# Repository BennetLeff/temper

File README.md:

# Temper — ESP32-S3 Induction Cooker

## Architecture

> Package inventory — boxes sized by lines of code, colored by language, with dependency arrows. The Mermaid diagram below shows data-flow relationships.

Temper is a consumer induction cooker built around three pillars: an
**ESP32-S3 firmware** with an 8-state transition-table machine handling
real-time power control and hardware-latched protection circuits; a **KiCad
PCB design** optimized through a custom CP-SAT-based signal-integrity and
thermal-aware placer pipeline; and a **Python/Rust placer toolchain**
(CP-SAT solver, geometry/DRC/DSN/IPC crates, workflow DAG) that automates layout
and checks placement against IPC standards. Protection — over-current,
over-voltage, thermal shutdown, UVLO — is *designed* to be hardware-latched with
firmware monitoring.

> **Implementation status is deliberately not summarized here.** As of this
> writing not all protection gates are implemented, and none has been validated
> on hardware. [`docs/STRATEGY.md`](docs/STRATEGY.md) holds the measured state
> and the gate matrix; it churns by design, and this file does not restate it.
> An earlier version of this paragraph asserted that all safety gates were
> hardware-latched and monitored, which was not true when written.

```mermaid
graph TD
  subgraph Firmware ["Firmware (ESP32-S3, C)"]
    SM[8-State Machine]
    PROT[Protection Circuits<br/>OCP OVP THM UVLO]
  end

  subgraph PCB ["PCB (KiCad)"]
    KICAD[Schematics & Layout]
  end

  subgraph Placer ["Placer (Python + Rust)"]
    CPSAT[CP-SAT Solver]
    RUST[Rust Crates<br/>Geometry DRC DSN IPC PCL-IR]
  end

  subgraph Pipeline ["Pipeline & CI"]
    DAG[temper-workflow DAG]
    REGR[Placer Regression]
    FW[Firmware Tests]
    PY[Python Tests]
  end

  SM --> PROT
  CPSAT --> RUST
  KICAD --> DAG
  RUST --> DAG
  DAG --> REGR
  FW --> DAG
  PY --> DAG
```

## Get Started in 60 Seconds

Build and run the firmware test suite:

```bash
cmake -B firmware/test/build firmware/test
cmake --build firmware/test/build
./firmware/test/build/test_state_machine_only
```

Or build and test the placer toolchain:

```bash
uv sync
uv run pytest packages/temper-placer/tests/
```

**Prerequisites:** CMake ≥ 3.16 and the ESP-IDF toolchain (see
[CONTRIBUTING.md](CONTRIBUTING.md) for full setup instructions).

## Reading Paths

### 5-Minute Overview

For anyone wanting to understand what Temper is and how it's structured:

- [docs/STRATEGY.md](docs/STRATEGY.md) — project approach, safety and performance gates
- Architecture diagram above — subsystem relationships at a glance
- [Project structure](#project-structure) — what lives where

### 30-Minute Build & Test

For developers ready to build, test, and navigate the codebase:

- [CONTRIBUTING.md](CONTRIBUTING.md) — development workflow, commit convention, codegen rules
- [AGENTS.md](AGENTS.md) — firmware build section; codegen and CI conventions
- [`.importlinter`](.importlinter) — package boundary contracts; verify with `uv run python scripts/import_linter_gate.py`
- [packages/temper-placer/tests/regression/](packages/temper-placer/tests/regression/) — placer regression test suite

### Deep-Dive Contributor

For contributors working on architecture, verification, or toolchain internals:

- [AGENTS.md](AGENTS.md) — full agent instructions, traceability convention, physics verification rules
- [docs/plans/](docs/plans/) — feature and improvement plans with requirements trace
- [docs/solutions/](docs/solutions/) — documented fixes for past bugs, patterns, and tooling decisions
- [docs/TRACEABILITY.md](docs/TRACEABILITY.md) — requirements-to-code traceability specification
- [docs/physics-verification-methodology.md](docs/physics-verification-methodology.md) — CP-SAT constraint soundness and validation framework

## Project Structure

<!-- BEGIN GENERATED: repo-map -- edits here are overwritten by scripts/gen_repo_state.py -->

*All 22 tracked top-level directories. Generated -- a new directory without a description fails CI.*

| Directory | Purpose |
|---|---|
| `.cargo/` | Cargo config -- macOS pyo3 `-undefined dynamic_lookup` link flags |
| `.github/` | CI workflows, issue templates, code owners |
| `benchmarks/` | CP-SAT benchmark harness and external board corpora manifests |
| `ci-corpus/` | Gate-mutation-testing corpus (canaries + mutations.yaml) for CI gates |
| `components/` | Local KiCad symbol/footprint libraries, one directory per part |
| `configs/` | Named placer configurations (deterministic, production) |
| `crates/` | Rust-only crates -- no pyproject.toml, outside the uv workspace. Where code lives once it no longer needs an interpreter: the temper binary and the CP-SAT FFI |
| `dashboard/` | Static HTML/JS dashboard for placer metrics |
| `datasheets/` | Vendor PDFs for parts used in the design |
| `docs/` | Plans, brainstorms, solutions, evidence, specs, and strategy |
| `elec/` | Atopile electrical source -- the schematic's source of truth |
| `firmware/` | ESP32-S3 firmware (C), 8-state machine and protection monitoring |
| `instruments/` | Measurement instrument designs, calibration procedures, and prototype fabrication files |
| `max31865/` | KiCad library for the MAX31865 RTD front-end (predates components/) |
| `metrics/` | Recorded routing/placement metric snapshots (JSON) |
| `output_gerbers/` | Exported Gerber/drill artifacts from a past routed revision |
| `packages/` | Python and Rust workspace members -- placer, DRC, geometry, router |
| `pcb/` | KiCad project: schematics, board, and project settings |
| `power_pcb_dataset/` | Regression corpus, baselines, and DRC ceilings |
| `scripts/` | CI gates, generators, and one-off analysis tooling |
| `simulation/` | ngspice models and protection-gate simulation harnesses |
| `tools/` | Developer utilities not wired into CI gates |

<!-- END GENERATED: repo-map -->

## Inventory

<!-- BEGIN GENERATED: inventory -- edits here are overwritten by scripts/gen_repo_state.py -->

**18 workspace packages** under `packages/`:

- `temper-constraint-compiler`
- `temper-data-model`
- `temper-design-bundle`
- `temper-drc-rs`
- `temper-geometry`
- `temper-io-types`
- `temper-orchestration`
- `temper-pcl-ir`
- `temper-placer`
- `temper-py-bridge`
- `temper-py-bridge-derive`
- `temper-quality-oracle`
- `temper-rust-router`
- `temper-rust-router-core`
- `temper-thermal`
- `temper-wasm-test-runner`
- `temper-worker`
- `temper-workflow`

Sizes and dependency edges are in [`ARCHITECTURE.svg`](./ARCHITECTURE.svg), regenerated automatically on push.

<!-- END GENERATED: inventory -->

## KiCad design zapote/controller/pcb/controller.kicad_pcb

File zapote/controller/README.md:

# Integrated SELV controller (schematic capture)

This is the induction cooktop's low-voltage controller, captured in atopile and laid out (layout L3: enclosure R33 delta on the R31 outline, the R36 rim NTC, and the L3 blower supply, NTC filters and thermal trip ladder; see [LAYOUT.md](LAYOUT.md)). The board integrates:
- an ESP32-S3-WROOM-1U-N8 (U.FL to an off-board chip antenna, enclosure R33);
- the interlock and thermal-sense circuits, ported unchanged;
- the RTD front end;
- the D-11 bus-voltage receiver;
- the buffers for the ADC channels;
- the 3.3 V supply and the adjustable 5.5–12 V blower supply with tach (L3, DECISIONS C28), the blower buck fed from its own 15 V supply PS3 through J13 (stage 16, C33);
- the probe connectors and one 12-way UI bus (J7, R33) to the fascia UI board, which carries the OLED, buttons, encoder and buzzer.

It draws all of its power from PS3 on J13 (C49: the logic rail `v15_selv` is fed from `V15_BLW` through D9, SS14) and supplies native-21's 3.3 V logic back through J4.3. J4.1 is not a supply since C49: it is `bias_good_j4` from the power board, read on GPIO35.

**Status:** schematic source, frozen netlist and a routed, DRC-clean layout candidate (0 errors, 0 unconnected, schematic parity 0; DFM, enclosure checks and fab review PASS) with a JLC fab package ([LAYOUT.md](LAYOUT.md)). **Candidate, not released**: ordering is the owner's decision. Not fabricated, no physical test. Open items and decisions are in [DECISIONS.md](DECISIONS.md). The connector list and placement note for the enclosure team are in [ENCLOSURE-HANDOFF.md](ENCLOSURE-HANDOFF.md).

**Requirement inputs** (read-only):
- `output/temper-manufacturing-r25/design/r25/CONTROLLER-ARCHITECTURE.md` and `CONTROLLER-SPEC.md`. They supersede r24 only in the harness landings.
- The R20 M1/M3, R21 N8 and R24 decisions.
- The native-21 J4 contract on branch `codex/power-stage-integration` @ `7c55c9ab8`, frozen into [inputs/native-21/](inputs/native-21/) with hashes in `provenance.json`. This covers `FAULT-INTERFACE.md`, DECISIONS (bus sense D-11, timing D-20, LINE_ZC, the 15 A input cap with its correction) and `firmware/components/power/include/{fullbridge_adapter,input_limits,line_zc}.h`.

## Layout of the unit

| Path | What |
|---|---|
| `elec/src/controller.ato` | Top module `SelvController`. One section per sheet: J4, power, trip glue, interlock, thermal, RTD, analog, MCU |
| `elec/src/controller_parts.ato` | New parts. Each docstring cites the datasheet pin table it was checked against |
| `elec/src/interlock_block.ato`, `thermal_block.ato` | Ported blocks, generated by `tools/port_blocks.py` (see below) |
| `elec/src/rtd_c1_block.ato` | `RTDSensingC1` (C37): the library `RTDSensing` plus the sensor-r3 CR-1 edits, generated by `tools/port_rtd_c1.py` (`--check` in the verifier) |
| `evidence/sensor-r3-checks/` | sensor-r3 `checks.py` (copied from sensor-c1-impulse-mining 1431caad5) and `run_as_built.py`, which runs it on the frozen netlist's values (`checks-as-built.json`) |
| `elec/src/{components,modules,footprints,interfaces,constraints,fac_utils}.ato`, `generics/` | Shared library, byte-identical to the RTD unit's source-04 set (`RTDSensing` lives in `modules.ato`) |
| `frozen/` | Reviewed build outputs (`default.net`, `default.csv`, `resolved-components.json`) with the unit path normalised to `UNIT`, plus `build-receipt.json` |
| `bom/controller-parts.json` | Every MPN with its LCSC code, JLC stock on 2026-10-08, origin and datasheet basis |
| `inputs/native-21/` | Frozen native-21 netlist, BOM and resolved export (the J4 and v3v3 counterpart) |
| `tools/verify_controller.py` | The verification (below); writes `evidence/verify.json` |
| `tools/controller_calcs.py` | Every numeric claim in these docs; writes `evidence/controller_calcs.json` |
| `tests/test_verify_mutations.py` | 50 tests. They miswire the frozen netlist and require the owning check to fail |
| `layout/` | Board build, router, enclosure/layout check, DFM gate and fab export; `python3 layout/make.py` runs the gates (see [LAYOUT.md](LAYOUT.md)) |
| `pcb/` | `controller.kicad_pcb` (routed board), `.kicad_pro`, the parity schematic, vendored footprints |
| `fab/` | Gerbers, drill, BOM/CPL with LCSC codes, assembly drawing, `fab-notes.md` (candidate, not released) |

**What "ported unchanged" means here:** `tools/port_blocks.py` copies `zapote/interlock/source-build-02/.../interlock_unit.ato` and `zapote/thermal-sense/source-build-02/.../thermal_sense_unit.ato` with one line filter. It drops only:
- the standalone inter-board headers (interlock J1/J2, thermal-sense J3);
- their pin joins;
- thermal-sense's `+3V3`/`gnd` net-name overrides.

`--check` proves that the committed files equal *source minus those lines*. The thermal probe connectors stay. Every value, MPN and internal connection is unchanged. `RTDSensing` is instantiated directly from the byte-identical library, so the RTD unit's 2×5 host header is not used.

## Build, freeze, verify

From `zapote/controller`. These use pinned atopile, are offline and build no Rust or workspace.

```sh
python3 tools/freeze.py            # ato build + circuit_export + normalise into frozen/ + receipt
python3 tools/freeze.py --check    # rebuild; fail if frozen/ is stale ("frozen fresh")
python3 tools/verify_controller.py # all checks on frozen/; exit 1 on any failure
python3 -m unittest discover -s tests -v
python3 tools/controller_calcs.py  # numeric basis only
python3 tools/snapshot_native21.py # re-derive inputs/native-21 from git (read-only)
```

- **Raw build:** `uv tool run --offline --from atopile==0.2.69 ato --non-interactive build elec/src/controller.ato:SelvController`.
- **Warnings:** the build emits only atopile's "Implicit Declaration" deprecation warnings for `override_net_name`, the same as the thermal-sense build.
- **Part identity:** it comes from `resolved-components.json` or the CSV, never from the netlist's `libsource` field. Atopile 0.2.69 aliases parts by footprint there; see the power-stage README.

**Current result** (frozen netlist sha256 `8471186c…`; 343 components, C51/C52): `VERIFY: PASS` (270 checks in 17 sections), and 50/50 mutation tests pass (2026-11-27).

| Section | Checks | What is asserted |
|---|---|---|
| sources | 5/5 | Ports equal their sources minus the boundary lines; `rtd_c1_block.ato` equals the library `RTDSensing` plus the listed C37 edits (`port_rtd_c1.py --check`). Library `modules/components/footprints.ato` hashes equal `zapote/rtd/circuit/rtd_contract.json` |
| j4 | 35/35 | All 16 pins carry exactly native-21's J4 net names. Both ends are Micro-Fit 3.0 2×8 headers (controller: right-angle 43045-1600 per R27; native-21: vertical 43045-1612) on a 1:1 harness. Pin obligations: J4.3 is the 3.3 V buck output; J4.1 feeds the 3.3 V buck only (stage 16: the blower buck is on PS3); each PWM line has a 10 kΩ pull-down and is driven from an MCU GPIO; PERMIT's only driver is the PERMIT gate U37 = latch Q AND RUN_EN (C23); bus_fault enters the interlock OCP input with its 10 kΩ pull-up; 11/12 enter the D-11 receiver; ct_mon sees one buffer input and ≥ 1 MΩ DC; ct_zc/line_zc reach GPIO38/39; returns 2/4/15 are on selv_gnd |
| adc1 | 26/26 | VBUS, CT_MON, HS, COIL, M12 and RIM (R36 rim NTC, GPIO9) each on one ADC1 pad, driven by its buffer; each NTC buffer input is an RC ≤ 1 kHz (C29). Six distinct channels; nothing analog on ADC2 or a strap; SPI 10–13 go to the RTD front end; the sample pattern fits (below) |
| trip | 24/24 | The structural and exhaustive interlock checks (below), with the C38 wiring: window branch on J3.2, runaway divider on J3.3, RTDIN± reaching J3 through the two-stage filter, the rim trip comparator's inputs |
| sensor_io | 6/6 | C37/C40: every J3 pin has its 220 nF and TVS to selv_gnd; J12 = RIM_SENSE / return / drain; each TVS's VRWM covers its line's maximum |
| capmode | 27/27 | C39 capacitive-mode detector: clocks from the inverted leg-A commands, D = CT_ZC through the polarity XOR, RUN_EN preset/clear, CAP_FAULT into the interlock OVP input, read-backs; a netlist-driven sequence simulation (inductive never faults, capacitive faults on the first edge, stuck / reversed CT, RUN_EN clears); the `capmode()` timing checks |
| v3v3 | 5/5 | Current budget for both boards, regulator, inductor, PS1 (logic only since stage 16: 4.83 W of 21 W at any blower speed), and the native-21 rail window |
| blower | 13/13 | J10 = V_BLOWER / GND / FG; FG pull-up, TVS and series R into GPIO3; GPIO46 PWM filtered into the blower buck's FB with full speed at reset; switch-off from expander P15 with the blower running at power-up; the `blower_supply()` sizing checks (C28) |
| blwin | 16/16 | Stage 16 (C33): J13 = V15_BLW / selv_gnd on a B2P-VH; U2's VIN, EN-divider top and input caps on V15_BLW; no part joins V15_BLW to v15_selv; 100 µF bulk on V15_BLW; BLW_PG 20 k / 4.7 k into expander P16; the `ps3_budget()` and `blw_pg()` checks (PS3 39.7 W of 60 W) |
| thermal | 11/11 | The thermal-sense comparator trips from the netlist resistor values, 64 corners (a port of the zapote-erc method): heatsink 101.4 °C (98.3–104.6) above the 95 °C firmware trip and with Tj ≤ 135 °C; coil 175.7 °C (169.7–182.0) above the 165 °C firmware trip; open/short margins (C32) |
| hs_adc | 9/9 | CR-8 (C45): HS_ADC = follower × r_hs_adc_bot / (r_hs_adc + r_hs_adc_bot) from the netlist values. The gain band (0.1 % + 25 ppm/K over 65 K) keeps the ADC below the calibrated 2.9 V from −40 to 150 °C at the 3.367 V rail (worst 2.877 V). Also checked: source and sampling error ≤ 0.1 K at 95 °C, follower load ≤ 1 mA. HS_SENSE carries exactly the thermal block's parts and r_hs_filt, so the hot and open comparators are untouched |
| ct_rms | 20/20 | The tank-RMS channel: ct_mon buffer → AC coupling → AD8436 (unity input buffer, AC-coupled core, single supply on v15, C0G CAVG) → gain-4 output buffer → 1 kΩ + BAT54S clamp → MCP3202 CH0. CH1 reads the LM4040 2.5 V reference. The ADC sits on the RTD SPI bus with its own pulled-up CS GPIO; the raw ct_mon ADC1 path is kept |
| ui | 25/25 | J7 (R33 UI bus, DECISIONS C26): exact 12-pin map with a GND beside every signal; each signal reaches its GPIO through one 33–100 Ω series resistor with nothing active on the connector side, and has an SRV05-4 clamp; the UI bus GPIOs (40/41/44/47/48/45) are disjoint from the RTD / MCP3202 SPI bus, which never reaches a connector; both chip selects pulled up; +5 V from the TLV76050 within its budget |
| bom | 2/2 | Every resolved MPN is in `bom/controller-parts.json` with a basis |
| misc | 8/8 | GPIO0 is pulled up and GPIO45/46 read 0 at reset; the PWM GPIOs have no reset pull-up; USB is on the TC2050 debug land; no switch on the board; EN and IO0 reach no connector but that land (C41) |

## Interlock trip path (hardware only)

**How the check works.** `verify_controller.py` builds a gate-level model from the captured netlist: LVC14, HC30, LVC1G74, the LVC1G08/32/38/14 gates and the LVC244 buffer, keyed by MPN pin tables. Comparators, supervisors, J4.10, the MCU and the I²C expander become free variables. The pass criterion is an **independent specification** of each source's healthy level (`tools/trip_sim.py`, `HEALTHY_LEVEL`), never the circuit's own internal nets.

**Structural checks:**
- PERMIT (J4.9) has one driver, the AND gate U37 (SN74LVC1G08): **PERMIT = latch Q AND RUN_EN** (DECISIONS C23). It has a 10 kΩ pull-down here (R103), and native-21 adds two 100 kΩ. The latch Q (`PERMIT_LATCH`) keeps the block's own 10 kΩ pull-down.
- The only firmware-driven nets in PERMIT's fan-in cone are `IL_RESET_N` (GPIO17, the reset request) and `RUN_EN` (GPIO14). RUN_EN feeds only the PERMIT gate (checked), has a 4.7 kΩ pull-down and no pull-up, and sits on a GPIO with no reset pull-up, so it reads "not permitted" at reset and with the MCU unpowered.
- No MCU or expander pin touches any other cone net. The MCU reads PERMIT, bus_fault, the supervisor output, RAIL_OK, LATCHED_FAULT and the three block faults only through the SN74LVC244A, so no GPIO misconfiguration can drive a protective net.
- The runaway comparator observes J3.2 (the connector-side S+) through the RTD block's window branch, and its threshold comes from the BIAS divider returned to J3.3 (S−, C38); the rim trip comparator compares the filtered rim NTC node with a v3v3 divider (checked, because comparators are free variables).
- The rail supervisor senses v3v3, and the watchdog's WDI is the MCU heartbeat.

**Exhaustive check.** All 2¹⁴ source combinations (C38 adds the rim trip, C39 the two capacitive-mode flip-flop outputs) × latch state × every RESET_N transition × RUN_EN (262 144 cases) were enumerated:
- every case with any source unhealthy leaves **PERMIT low**, whatever firmware does;
- PERMIT is never high while the latch is tripped or RUN_EN is low (`run_en_alone_cannot_assert_permit`): RUN_EN can only remove permission;
- all-healthy plus a fresh RESET_N falling edge with RUN_EN high grants PERMIT;
- all-healthy with no edge holds the latch state.

**Single-cause truth table.** Each row has every other source healthy and RUN_EN high, and starts from PERMIT high. The result is identical for RESET_N held low, held high, falling or rising.

| Trip source (net → interlock input) | Fault level | PERMIT | LATCHED_FAULT |
|---|---|---|---|
| J4.10 `bus_fault` (native-21 OR of OCP, OVP, HOT5, CT±; an open wire reads high via the 10 kΩ pull-up) → OCP | high/open | 0 | 1 |
| `CAP_FAULT` (C39): a capacitive-mode sample on a leg-A turn-off (U42 1Q̄ or 2Q) → OVP input | high | 0 | 1 |
| thermal `HS_HOT` or `HS_OPEN` → HS_FAULT (LVC1G32) → heatsink | high | 0 | 1 |
| thermal `COIL_HOT` or `COIL_OPEN` → COIL_FAULT → coil | high | 0 | 1 |
| RTD low/high window out of range, or `RTD_RAIL_OK` low → RTD_HW_FAULT (open-drain NAND) → RTD | low | 0 | 1 |
| `RUNAWAY_FAULT`: pan ≥ 298.8–323.1 °C (C38), MAX31865 BIAS off, or RTD open; or the rim NTC ≥ 262.1–288.3 °C or shorted (U40, C38) → runaway | high | 0 | 1 |
| `RAIL_OK` low (v3v3 outside 3.146–3.190 / 3.408–3.456 V, or within 10 ms of start-up) → RAIL_FAULT → AUX, and SENSOR_LIVE low | low | 0 | 1 |
| `RTD_RAIL_OK` low (RTD_AVDD below its 3.05 V supervisor) → SENSOR_LIVE low (and RTD_HW_FAULT) | low | 0 | 1 |
| Supervisor run-OK `WDT_RESET_N` low (TPS3823: WDI not toggled within 0.9 s minimum, or VDD below its 2.83–3.00 V threshold, SLVS165O) | low | 0 | 1 |
| All healthy, RESET_N held | — | holds | holds |
| All healthy for ≥ 1 ms, then a fresh RESET_N falling edge | — | 1 | 0 |

The simulation treats the sources as independent. Physical paths that make several assert together, like v3v3 loss, are covered by the FMEA in DECISIONS.md.
- **Loss of v3v3 or selv_gnd, or J4 unplugged:** the latch loses supply, the controller's 10 kΩ and native-21's 100 kΩ pull-downs take PERMIT low, and a broken J4.10 conductor reads as a fault.
- **Firmware reach:** it can read the latch, request a reset edge and drop RUN_EN (a fast stop that removes PERMIT without tripping the latch). It cannot hold the latch clear, assert PERMIT while the latch is tripped, or override a trip.

## Power tree

```
PS3 15 V on J13 V15_BLW ── D9 SS14 (C49) ── v15_selv ── 100 µF + 2×(10 µF‖100 nF)    [logic only, 4.83 W]
  ├─ U1 TPS62933F (FCCM, 500 kHz, EN UVLO on 10.9–12.1 V, off ≥ 9.8 V), 10 µH, 3×22 µF
  │    └─ v3v3 3.304 V nom (3.242–3.367 V, 0–85 °C)
  │         ├─ ESP32-S3-WROOM-1U-N8, J7.2 to the UI board (OLED, expander, encoder, buzzer), expander, buffers, D-11 receiver, MCP3202
  │         ├─ interlock / thermal-sense / RTD blocks (RTD analogue behind its ferrite → RTD_AVDD)
  │         ├─ U3 TPS3703A4330-Q1 window supervisor (SENSE via 1 k / 1 µF) → RAIL_OK
  │         └─ J4.3 → native-21 SELV logic (u_fault_or, 4× ISO7710, AMC1311 VDD2, UCC21550 VCCI …)
  ├─ U14 AD8436 tank-RMS converter (single supply, ≈ 0.64 mA)
  └─ 2 × 100 Ω → U16 TLV76050 → V5_UI (J7 pin 1, ≤ 30 mA for a 5 V encoder; current-limited)

PS3 MPM-90-15ST (chassis, 15 V, 85 W; C51; IRM-60-15ST at stage 16, C33) ── J13 (B2P-VH) V15_BLW ── 100 µF + 3 input caps
  ├─ 20 k / 4.7 k → BLW_PG → expander P16 (PS3 present)
  └─ U2 TPS62933 (500 kHz), 10 µH SWRB1205S, 2×22 µF → V_BLOWER 5.0–12.4 V (PWM into FB) → J10 blower (1.42 A typ, 2.70 A max)
       EN defaults on (UVLO follows PS3); firmware sets speed (GPIO46 PWM, full speed by default) and can switch it off (Q1 from expander P15)
```

**v3v3 budget**, from datasheet maxima at 3.465 V (`evidence/verify.json`, rows per part):

| Load | mA |
|---|---|
| Controller board, all parts on v3v3. Includes the ESP32 at 500 mA (Espressif's ≥ 0.5 A supply requirement; TX peak 355 mA), MAX31865 9.65 mA with BIAS, OPA2388 5.2 mA, the interlock WDI 1 kΩ pull-down 3.5 mA, and pull-ups at full current | 537.3 |
| native-21 on J4.3 and on controller-driven J4 lines (UCC21550 VCCI, AMC1311, 4× ISO7710, DIS pull-ups, INx 50 kΩ min, PERMIT gate networks). Computed from its frozen netlist; every v3v3 part must be modelled or the check fails | 49.4 |
| OLED NHD-3.12-25664UCW2 on the UI board via J7.2, 100 % on (Newhaven IDD max) | 340 |
| UI board allocation on J7.2 [UNVERIFIED parts]: 30 mA logic + 3.3 V encoder option, 90 mA buzzer (the 5 V option is also counted on 15 V in the PS1 figure) | 120 |
| **Peak** | **1047** |

- **Converter limits:** the TPS62933F is good for 3 A and SWPA6045S100MT for 2.45 A Irms (3.5 A sat).
- **PS3 (C49, logic and blower on one supply):** merged continuous load 44.55 W against 65 W, 99 % of the 45 W 60 °C derated figure (`tools/controller_calcs.py` `merge_rail`; DECISIONS C49). The PS1 figures that stood here were for the pre-C49 board, which had a separate 21 W logic supply.
- **Own load:** with the fan excluded, the controller's own load stays under the spec's ≈ 4 W even at peak.
- **Native-21's rail:** it sees 3.237–3.389 V at its J4.3. That covers regulator tolerance, the J4 harness (≤ 1 m AWG22, two 10 mΩ contacts per conductor; an allocation, because the harness isn't specified) and ground shift from the 15 V return. This is inside the 3.135–3.465 V contract.

**Rail window** (`tools/controller_calcs.py`):
- **Thresholds:** the TPS3703A4330 trips UV at 3.146–3.190 V and OV at 3.408–3.456 V, both inside the contract.
- **Regulator corners:** the low corner clears the UV *release* threshold (≤ 3.217 V) by 21 mV, so RESET always releases after start-up.
- **Margins left** for excursions slower than the 1 ms SENSE filter: 47 mV (low) and 39 mV (high). Faster Wi-Fi/OLED load steps are filtered.
- **Bench item:** measure supervisor nuisance trips under combined ESP32-TX and OLED-on steps.

## ADC1 and sampling

| GPIO | ADC1 | Signal | Source | Attenuation |
|---|---|---|---|---|
| 1 | CH0 | CT_MON_ADC | TLV9062 follower of J4.14 ct_mon (≥ 10 MΩ DC load), 100 Ω / 1 nF | ATTEN3 (0–2.9 V) |
| 2 | CH1 | VBUS_ADC | D-11 OPA2388 half-gain difference receiver, 100 Ω / 100 nF | ATTEN2 (0–1.6 V) |
| 6 | CH5 | HS_ADC | TLV9062 follower of thermal-sense HS_SENSE | ATTEN3 |
| 7 | CH6 | COIL_ADC | TLV9062 follower of COIL_SENSE | ATTEN3 |
| 8 | CH7 | M12_ADC | TLV9062 follower of the M12 probe divider | ATTEN3 |

**Free ADC1 pads:** GPIO3, 4, 5, 9 and 10 are used digitally. GPIO3 is fan tach (a strap, harmless unless the JTAG eFuse is burnt). GPIO4/5 are PWM, GPIO9 is I²C SDA and GPIO10 is RTD CS. So **ADC1 is full**: the tank-RMS signal therefore goes to an external MCP3202 on the RTD SPI bus (below).

**Tank RMS (external ADC).** U14 AD8436BRQZ converts the buffered ct_mon to true RMS. Its datasheet gives 65 kHz for 1 % additional error at 300 mV rms, against a 31–55 kHz tank band.
- **Scaling:** a gain-4 output buffer puts 22 A RMS tank at 1.32 V (1606 codes) and the 55 A peak trip at 2.33 V.
- **Errors:** coupling error at 31 kHz is 0.002 %; Schottky leakage contributes ≤ 0.15 %.
- **Settling:** CAVG = 100 nF C0G gives an estimated 3.4 ms to 0.1 %, falling. That is the datasheet's 10 µF figure scaled linearly; the scaling is an assumption to bench-check. It is within the 8.3 ms half-cycle.
- **ADC:** U15 MCP3202 CH0 reads it; CH1 reads the LM4040A25 2.5 V (0.1 %) so firmware removes the v3v3-as-reference error. CS is GPIO42. The bus stays on the board; the UI board has its own SPI host (C26).
- **Why not ADC2:** the free ADC2 pads are the debug USB pins, and ADC2 cannot be read while Wi-Fi runs.

The raw ct_mon ADC1 path stays for phase and waveform checks.

**Sampling plan.** It is checked against ESP-IDF v5.2.3 `SOC_ADC_SAMPLE_FREQ_THRES_HIGH` = 83 333 S/s and the datasheet's 100 kS/s.
- **Continuous pattern** at 80 kS/s: `VBUS, CT_MON, VBUS, CT_MON, VBUS, HS, COIL, M12, RIM` (RIM: R36 rim NTC, C27).
- **Resulting rates:** VBUS 26.7 kS/s (≥ 20 kS/s required) with a largest gap of 62.5 µs (≤ 150 µs freshness), CT_MON 17.8 kS/s, and the four temperatures 8.9 kS/s each.

**D-11 receiver:**
- **At the ADC:** 0.248 V at 0 V bus, 0.956 V at 170 V and 1.073 V at 198 V.
- **Over-range:** the 1210 mV over-range latch corresponds to a 231 V bus.

## Part choices (summary; the reasons are in DECISIONS.md)

| Function | Part | Why |
|---|---|---|
| MCU | ESP32-S3-WROOM-1U-N8 (C2980297) | Required family (the round-5 firmware targets the S3-WROOM-1-N8; the -1U has the same pins). No octal PSRAM, so GPIO35–37 are free. R33: U.FL to the off-board chip antenna |
| 3.3 V | TPS62933FDRLR (C5219272) | 3.8–30 V, 3 A, ±1.5 % VFB. Forced-CCM gives predictable ripple. Shares a die with the fan buck |
| Blower supply | TPS62933DRLR (C3200405) + SWRB1205S-100MT 10 µH (C169383) | 3 A class, 4.2–5.8 A high-side limit; the 4 A-rated inductor carries the blower's 2.70 A maximum. Speed by PWM into FB; full speed by default (C28) |
| Rail window | TPS3703A4330DSERQ1 (C1850327) | ±0.7 % fixed ±4 % window, the only class that fits inside 3.135–3.465 V around a ±1.5 % regulator. The TPS3700 (±1.7 %) does not. Q1 grade fitted because the commercial part had zero JLC stock; SBVS344D confirms identical pins, thresholds and delay |
| Tank RMS | AD8436BRQZ (C652840) | Datasheet bandwidth 65 kHz for 1 % error, the only candidate whose datasheet I could read that covers 55 kHz on our supplies. The LTC1968 is 500 kHz per ADI's product page, but its 4.5–5.5 V supply and unread datasheet ruled it out. **JLC stock 0: consign** |
| External ADC | MCP3202-CI/SN (C56997) | 2-channel 12-bit SPI at 3.3 V; shares the RTD bus |
| UI bus protection | 6 × 100 Ω series, 2 × SRV05-4 (C2836319), TLV76050 (C2867465) | Source termination and ESD current limit on a 120 mm jumper; ±12 kV contact clamps; ≤ 30 mA +5 V for a 5 V encoder |
| Bus receiver | OPA2388IDR + LM4040A25 + RT0603 0.1 % | The D-11 circuit as specified |
| Analog buffers | 2× TLV9062IDR (C398355) | CMOS, 0.5 pA typical bias. Gives the thermal-sense nodes a receiver that stays within their ±1 µA budget and isolates ADC switched-capacitor kick |
| Read-back isolation | SN74LVC244APWR (C7668) | One part buffers all eight protective read-backs; Ioff |
| SENSOR_LIVE, AUX | SN74LVC1G08, SN74LVC1G14 | — |
| Runaway | TLV3201AIDBVR + RT0603 20k/10k 0.1 % | Same comparator as the RTD and thermal blocks |
| I/O expander | TCA9555PWR (C465732) | Four fault read-backs and RTD_DRDY; P00–P06, P14–P17 spare since R33 |
| J4 | Molex 43045-1600 right-angle (C277731) | R27: right edge, mating +X; same Micro-Fit circuit numbering as native-21's 43045-1612. Envelope fit against Molex's drawing is [UNVERIFIED] (drawing not reachable) |
| UI bus (R33) | JST B12B-XH-A (C158027) | J7, one 12-way jumper to the fascia UI board (pin map in DECISIONS C26) |
| Other connectors | JST XH (B2B/B3B/B4B/B12B) | The thermal-sense and RTD units already use XH |

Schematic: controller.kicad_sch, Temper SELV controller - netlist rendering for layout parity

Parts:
C1, C9: UCD1E101MCL6GS; CP_Elec_8x6.2; MPN UCD1E101MCL6GS
C2, C11, C120: CL10B103KB8NNNC; C_0603_1608Metric; MPN CL10B103KB8NNNC
C3, C5, C12, C14, C20, C52, C53, C54, C55, C56, C57, C58, C59, C60, C61, C62, C63, C65, C66, C67, C68, C69, C70, C71, C72, C73, C74, C75, C76, C77, C78, C79, C85, C90, C92, C93, C94, C110, C111, C112, C113, C114, C115, C121, C123, C126: CC0603KRX7R9BB104; C_0603_1608Metric; MPN CC0603KRX7R9BB104
C4, C13, C15, C122, C143: CL31A106KAHNNNE; C_1206_3216Metric; MPN CL31A106KAHNNNE
C6, C7, C8, C89: CL21A226MAQNNNE; C_0805_2012Metric; MPN CL21A226MAQNNNE
C10, C19, C83, C86, C88, C91, C95, C96: CL10A105KB8NNNC; C_0603_1608Metric; MPN CL10A105KB8NNNC
C16, C17, C124, C125: CL31A226KAHNNNE; C_1206_3216Metric; MPN CL31A226KAHNNNE
C18, C64, C97, C118, C119, C127: CL10C102JB8NNNC; C_0603_1608Metric; MPN CL10C102JB8NNNC
C21, C22, C23, C24, C25, C26, C27, C28, C29, C30, C32, C33, C34, C35, C36, C37, C46, C47, C48, C49, C50, C51: C0603C104K5RACTU; C_0603_1608Metric; MPN C0603C104K5RACTU
C31, C38, C80, C81, C82, C116, C117: GRM31C5C1H104JA01L; C_1206_3216Metric; MPN GRM31C5C1H104JA01L
C39, C40: C0603C102J5GACTU; C_0603_1608Metric; MPN C0603C102J5GACTU
C41, C84, C87: GRM1885C1H103JA01D; C_0603_1608Metric; MPN GRM1885C1H103JA01D
C42, C43, C44, C45: CC0603KRX7R9BB224; C_0603_1608Metric; MPN CC0603KRX7R9BB224
D1, D2, D3, D4, D5, D6, D15: ESD5Z3.3T1G; D_SOD-523; MPN ESD5Z3.3T1G
D7, D14: ESD5Z5.0T1G; D_SOD-523; MPN ESD5Z5.0T1G
D8: BAT54S-7-F; SOT-23; MPN BAT54S-7-F
D9: SS14; D_SMA; MPN SS14
D10, D11, D12, D13: BAV199-7-F; SOT-23; MPN BAV199-7-F
J1, J2: B2B-XH-A(LF)(SN); JST_XH_B2B-XH-A_1x02_P2.50mm_Vertical; MPN B2B-XH-A(LF)(SN)
J3, J9: B4B-XH-A(LF)(SN); JST_XH_B4B-XH-A_1x04_P2.50mm_Vertical; MPN B4B-XH-A(LF)(SN)
J4: 0430451600; Molex_Micro-Fit_3.0_43045-1600_2x08_P3.00mm_Horizontal; MPN 0430451600
J7: B12B-XH-A(LF)(SN); JST_XH_B12B-XH-A_1x12_P2.50mm_Vertical; MPN B12B-XH-A(LF)(SN)
J10, J12: B3B-XH-A(LF)(SN); JST_XH_B3B-XH-A_1x03_P2.50mm_Vertical; MPN B3B-XH-A(LF)(SN)
J11: TC2050-IDC-NL-LAND; Tag-Connect_TC2050-IDC-NL_2x05_P1.27mm_Vertical; MPN TC2050-IDC-NL-LAND
J13: B2P-VH(LF)(SN); JST_VH_B2P-VH_1x02_P3.96mm_Vertical; MPN B2P-VH(LF)(SN)
J14: B2B-PH-K-S(LF)(SN); JST_PH_B2B-PH-K_1x02_P2.00mm_Vertical; MPN B2B-PH-K-S(LF)(SN)
J15: B5B-XH-A(LF)(SN); JST_XH_B5B-XH-A_1x05_P2.50mm_Vertical; MPN B5B-XH-A(LF)(SN)
L1, L3: SWPA6045S100MT; L_Sunlord_SWPA6045S; MPN SWPA6045S100MT
L2: SWRB1205S-100MT; L_Sunlord_SWRB1205S; MPN SWRB1205S-100MT
Q1: 2N7002; SOT-23; MPN 2N7002
Q2: BSS138LT1G; SOT-23; MPN BSS138LT1G
R1, R2, R3, R4, R42, R43, R44, R45, R107: RC0603FR-0733RL; R_0603_1608Metric; MPN RC0603FR-0733RL
R5, R6, R7, R8, R19, R25, R28, R29, R33, R55, R56, R61, R62, R63, R64, R65, R66, R67, R68, R70, R71, R74, R75, R88, R91, R94, R97, R103, R108, R109, R119, R120, R124, R136, R154, R155, R156, R157: RC0603FR-0710KL; R_0603_1608Metric; MPN RC0603FR-0710KL
R9, R10, R26, R27, R69, R82, R106, R132, R133, R134, R135, R158: RC0603FR-071KL; R_0603_1608Metric; MPN RC0603FR-071KL
R11, R17, R20, R38, R51, R52, R73, R110, R150: RC0603FR-07100KL; R_0603_1608Metric; MPN RC0603FR-07100KL
R12, R18, R21, R151: RC0603FR-0712K1L; R_0603_1608Metric; MPN RC0603FR-0712K1L
R13: RT0603BRD0722K1L; R_0603_1608Metric; MPN RT0603BRD0722K1L
R14, R35: RT0603BRD077K06L; R_0603_1608Metric; MPN RT0603BRD077K06L
R15: RC0603FR-0720KL; R_0603_1608Metric; MPN RC0603FR-0720KL
R16, R102, R111, R112: RC0603FR-074K7L; R_0603_1608Metric; MPN RC0603FR-074K7L
R22: RC0603FR-0756K2L; R_0603_1608Metric; MPN RC0603FR-0756K2L
R23, R36, R152: RT0603BRD07140KL; R_0603_1608Metric; MPN RT0603BRD07140KL
R24: RT0603BRD0711K5L; R_0603_1608Metric; MPN RT0603BRD0711K5L
R30: RC0603FR-0711K5L; R_0603_1608Metric; MPN RC0603FR-0711K5L
R31: RT0603BRD078K06L; R_0603_1608Metric; MPN RT0603BRD078K06L
R32: AF0603FR-0734K8L; R_0603_1608Metric; MPN AF0603FR-0734K8L
R34, R83: RT0603BRD0790K9L; R_0603_1608Metric; MPN RT0603BRD0790K9L
R37: RC0603FR-071K21L; R_0603_1608Metric; MPN RC0603FR-071K21L
R39: PTFR0805B430RN9; R_0805_2012Metric; MPN PTFR0805B430RN9
R40, R41: RC0603FR-07499KL; R_0603_1608Metric; MPN RC0603FR-07499KL
R46, R131: BLM18AG121SN1D; L_0603_1608Metric; MPN BLM18AG121SN1D
R47: RT0603BRD0761K9L; R_0603_1608Metric; MPN RT0603BRD0761K9L
R48, R50, R54: ERA-3AEB103V; R_0603_1608Metric; MPN ERA-3AEB103V
R49, R90: ERA-3AEB5901V; R_0603_1608Metric; MPN ERA-3AEB5901V
R53: RT0603BRD0716K5L; R_0603_1608Metric; MPN RT0603BRD0716K5L
R57, R58, R59, R60, R89, R96, R139, R140, R141, R142: RT0603BRD071KL; R_0603_1608Metric; MPN RT0603BRD071KL
R72: RC0603JR-070RL; R_0603_1608Metric; MPN RC0603JR-070RL
R76, R78, R79: RT0603BRD0720KL; R_0603_1608Metric; MPN RT0603BRD0720KL
R77, R80, R81, R84, R100, R105, R153: RT0603BRD0710KL; R_0603_1608Metric; MPN RT0603BRD0710KL
R85, R87, R92, R95, R98, R113, R114, R115, R116, R117, R118: RC0603FR-07100RL; R_0603_1608Metric; MPN RC0603FR-07100RL
R86, R101: RC0603FR-0710ML; R_0603_1608Metric; MPN RC0603FR-0710ML
R93: RT0603BRD0747KL; R_0603_1608Metric; MPN RT0603BRD0747KL
R99: RT0603BRD0786K6L; R_0603_1608Metric; MPN RT0603BRD0786K6L
R104: RT0603BRD0730KL; R_0603_1608Metric; MPN RT0603BRD0730KL
R121, R122: RC1206FR-07100RL; R_1206_3216Metric; MPN RC1206FR-07100RL
R123, R137, R138: RC0603FR-071ML; R_0603_1608Metric; MPN RC0603FR-071ML
R130: RT0805BRD074K3L; R_0805_2012Metric; MPN RT0805BRD074K3L
U1: TPS62933FDRLR; SOT-583-8; MPN TPS62933FDRLR
U2, U51: TPS62933DRLR; SOT-583-8; MPN TPS62933DRLR
U3: TPS3703A4330DSERQ1; WSON-6_1.5x1.5mm_P0.5mm; MPN TPS3703A4330DSERQ1
U4: ESP32-S3-WROOM-1U-N8; ESP32-S3-WROOM-1U; MPN ESP32-S3-WROOM-1U-N8
U5: OPA2388IDR; SOIC-8_3.9x4.9mm_P1.27mm; MPN OPA2388IDR
U6, U7: TLV9062IDR; SOIC-8_3.9x4.9mm_P1.27mm; MPN TLV9062IDR
U8: TCA9555PWR; TSSOP-24_4.4x7.8mm_P0.65mm; MPN TCA9555PWR
U9: SN74LVC244APWR; TSSOP-20_4.4x6.5mm_P0.65mm; MPN SN74LVC244APWR
U10, U17, U18, U31, U32, U40: TLV3201AIDBVR; SOT-23-5; MPN TLV3201AIDBVR
U11, U25, U33, U37: SN74LVC1G08QDBVRQ1; SOT-23-5; MPN SN74LVC1G08QDBVRQ1
U12, U45, U46: SN74LVC1G14DBVR; SOT-23-5; MPN SN74LVC1G14DBVR
U13: LM4040A25IDBZR; SOT-23; MPN LM4040A25IDBZR
U14: AD8436ARQZ-R7; QSOP-20_3.9x8.7mm_P0.635mm; MPN AD8436ARQZ-R7
U15: MCP3202-CI/SN; SOIC-8_3.9x4.9mm_P1.27mm; MPN MCP3202-CI/SN
U16: TLV76050DBZR; SOT-23; MPN TLV76050DBZR
U19, U26: TLV9031DBVR; SOT-23-5; MPN TLV9031DBVR
U20: SN74LVC1G74DCUR; VSSOP-8_2.3x2mm_P0.5mm; MPN SN74LVC1G74DCUR
U21: TPS3823-33DBVR; SOT-23-5; MPN TPS3823-33DBVR
U22: 74HC30PW,118; TSSOP-14_4.4x5mm_P0.65mm; MPN 74HC30PW,118
U23, U24: SN74LVC14ADR; SOIC-14_3.9x8.7mm_P1.27mm; MPN SN74LVC14ADR
U27, U28, U41, U44: SN74LVC1G32DBVR; SOT-23-5; MPN SN74LVC1G32DBVR
U29: REF2025AIDDCR; SOT-23-5; MPN REF2025AIDDCR
U30, U50: MAX31865AAP+T; SSOP-20_5.3x7.2mm_P0.65mm; MPN MAX31865AAP+T
U34: TPS389001DSER; TPS389001DSER_WSON-6_DSE; MPN TPS389001DSER
U35: SN74LVC1G38DBVR; SOT-23-5; MPN SN74LVC1G38DBVR
U36: TLV9061IDBVR; SOT-23-5; MPN TLV9061IDBVR
U38, U39: SRV05-4; SOT-23-6; MPN SRV05-4
U42: SN74LVC74APWR; TSSOP-14_4.4x5mm_P0.65mm; MPN SN74LVC74APWR
U43: SN74LVC1G86DBVR; SOT-23-5; MPN SN74LVC1G86DBVR
U52: EMC2301-1-ACZL-TR; MSOP-8_3x3mm_P0.65mm; MPN EMC2301-1-ACZL-TR

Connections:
BAY_ADC: C73.1, R95.2, U4.12
BIAS_GOOD_RB: C97.1, R123.1, R124.2, U4.28
BLW_PG: R15.2, R16.1, U8.19
BUS_FAULT_RB: U4.23, U9.16
CAP_FAULT: R62.2, U23.3, U44.4
CM_CLK_HA: U42.3, U45.4
CM_CLK_LA: U42.11, U46.4
CM_FAULT_HA: U42.6, U44.1
CM_FAULT_LA: U42.9, U44.2
CM_HA_OK_RB: R74.2, U8.4
CM_LA_OK_RB: R75.2, U8.5
CM_ZC: U42.2, U42.12, U43.4
COIL_ADC: C71.1, R92.2, U4.7
COIL_FAULT: R64.2, U9.17, U23.9, U28.4
COIL_FAULT_RB: U8.16, U9.3
COIL_HOT: R36.2, U18.1, U28.1
COIL_OPEN: U26.1, U28.2
COIL_REF: R34.2, R35.1, R36.1, U18.3
COIL_SENSE: C23.1, J1.1, R33.2, R91.1, U18.4, U26.3
CT_MON_ADC: C64.1, R87.2, U4.39
CT_RMS_ADC: C87.1, D8.3, R106.2, U15.2
CT_RMS_CORE: C84.1, U14.10, U14.13
CT_ZC_MCU: R9.2, U4.31
EXT_ADC_CS_N: R108.2, U4.35, U15.1
FAN2_ALERT: R155.2, U8.20, U52.8
FAN2_PWM: Q2.2, R156.2, U52.5
FAN2_TACH: C127.1, R158.2, U52.6
FAN_OFF: Q1.1, R19.1, U8.18
FAN_PWM: R20.1, R21.1, U4.16
FAN_TACH: C18.1, R26.2, U4.15
HS_ADC: C67.1, R89.2, R90.1, U4.6
HS_FAULT: R63.2, U9.15, U23.5, U27.4
HS_FAULT_RB: U8.15, U9.5
HS_HOT: R32.2, U17.1, U27.1
HS_OPEN: U19.1, U27.2
HS_REF: R30.2, R31.1, R32.1, U17.3
HS_SENSE: C21.1, J2.1, R29.2, R88.1, U17.4, U19.3
I2C_SCL_BOOT: J11.3, R111.2, U4.27, U8.22, U52.2
I2C_SDA: R112.2, U4.30, U8.23, U52.1
IL_RESET_N: R68.2, U4.10, U24.5
IL_WDI: R69.1, U4.11, U21.4
J7_CS_EXP_N: J7.12, R117.2, U39.3
J7_CS_OLED_N: J7.9, R116.2, U38.6
J7_DC: J7.10, R118.2, U39.1
J7_MISO: J7.7, R115.2, U38.4
J7_MOSI: J7.6, R114.2, U38.3
J7_SCK: J7.4, R113.2, U38.1
J10_FG: D1.1, J10.3, R25.2, R26.1
J15_FG: D15.1, J15.3, R157.2, R158.1
J15_PWM: D14.1, J15.4, Q2.3
LATCHED_FAULT_RB: U8.13, U9.9
LINE_ZC_MCU: R10.2, U4.32
MCU_EN: C91.1, J11.2, R109.2, U4.3
OPEN_REF: R37.2, R38.1, U19.4, U26.4
PERMIT_LATCH: R71.1, U20.5, U37.1
PERMIT_RB: U4.29, U9.18
RAIL_FAULT: R67.2, U12.4, U24.1
RAIL_OK: R28.2, U3.4, U9.8, U11.1, U12.2
RAIL_OK_RB: U8.6, U9.12
RIM_ADC: C76.1, R98.2, U4.17
RIM_HOT: U40.1, U41.2
RIM_SENSE: D7.1, J12.1, R96.2, R97.1
RIM_TRIP_TH: C78.1, R99.2, R100.1, U40.3
RTD2_AVDD: C110.1, C143.1, D10.2, D11.2, D12.2, D13.2, R131.2, U50.3
RTD2_CS_N: R135.1, R136.2, U8.10
RTD2_DRDY: U8.9, U50.1
RTD_AVDD: C29.1, C33.1, C34.1, C35.1, R46.2, R53.1, U30.3, U31.5, U32.5, U33.5
RTD_CS_N: R44.1, U4.18
RTD_DRDY: U8.11, U30.1
RTD_FAULT_RB: U8.14, U9.7
RTD_RAIL_OK: R55.2, U11.2, U34.6, U35.2
RTD_SCK: R42.1, R132.1, U4.19, U15.7
RTD_SDI: R43.1, R133.1, U4.21, U15.5
RTD_SDO: R45.2, R107.2, R134.2, U4.20
RUNAWAY_FAULT: R66.2, U23.13, U41.4
RUNAWAY_RTD: U10.1, U41.1
RUNAWAY_TH: C59.1, R76.2, R77.1, U10.4
RUN_EN: R102.1, U4.22, U37.2, U42.4, U42.13
SENSOR_LIVE: R70.1, U11.4, U24.9
SUP_RUN_OK_RB: U8.17, U9.14
UART0_TX: J11.4, U4.37
UI_CS_EXP_N: R117.1, R120.2, U4.25
UI_CS_OLED_N: R116.1, R119.2, U4.24
UI_DC: R110.1, R118.1, U4.26
UI_MISO: R115.1, U4.36
UI_MOSI: R114.1, U4.34
UI_SCK: R113.1, U4.33
USB_DN: J11.6, U4.13
USB_DP: J11.7, U4.14
V5_UI: C96.1, J7.1, U16.1
V12_FAN2: C124.1, C125.1, J15.2, L3.2, R152.1
V15_BLW: C9.1, C13.1, C14.1, C15.1, C122.1, C123.1, D9.2, J13.1, R15.1, R17.1, R150.1, U2.3, U51.3
VBUS_ADC: C62.1, R85.2, U4.38
V_BLOWER: C16.1, C17.1, J10.1, L2.2, R23.1
all_good: U20.6, U24.4
any_fault: U22.8, U24.3
aux_healthy: U22.11, U24.2
bay_buf_out: R95.1, U7.6, U7.7
bay_fan.u_buck-rt: U51.1
bay_filt: C72.1, R94.2, U7.5
bay_node: D6.1, J14.1, R93.2, R94.1
bias_good_j4: J4.1, R124.1
bst: C121.1, U51.6
bst_3v3: C3.1, U1.6
bst_12: C12.1, U2.6
bus_fault: J4.10, R61.2, U9.4, U23.1
ccf: U14.19
clk: R154.1, U52.7
cm_ha_ok: R74.1, U42.5
cm_la_ok: R75.1, U42.8
cm_zc_pol: R72.1, R73.2, U43.2
coil_buf_out: R92.1, U7.1, U7.2
coil_filt: C68.1, R91.2, U7.3
coil_healthy: U22.4, U23.8
common_good: U22.12, U25.4
ct_buf_out: C80.1, R87.1, U6.1, U6.2
ct_mon: J4.14, R86.1, U6.3
ct_zc: J4.13, R9.1, U43.1
dnc2: U14.2
dnc8: U14.8
dout: R107.1, U15.6
en: R150.2, R151.1, U51.2
en_3v3: R11.2, R12.1, U1.2
en_12: Q1.3, R17.2, R18.1, U2.2
fan_ctl: C10.1, R21.2, R22.1
fb: R152.2, R153.1, U51.8
fb_3v3: R13.2, R14.1, U1.8
fb_12: R22.2, R23.2, R24.1, U2.8
hs_buf_out: R89.1, U6.6, U6.7
hs_filt: C65.1, R88.2, U6.5
hs_healthy: U22.3, U23.6
ibufgn: U14.7
inn: R47.2, R48.1, U31.4
int: U8.1
io3: U39.4
io4: U39.6
latched_fault: U9.11, U20.3
line: R56.2, R65.2, U9.13, U23.11, U35.4
line_zc: J4.16, R10.1
live_buf: U24.10, U25.2
live_n: U24.8, U24.11
mr: U3.6
nc9: U22.9
nc10: U22.10
nc13: U22.13
ocp_healthy: U22.1, U23.2
ovp_healthy: U22.2, U23.4
p1: R39.1, R40.2, R41.2, R76.1, U30.4, U30.5
p03: U8.7
p04: U8.8
p9: J11.9
p10: J11.10
permit: J4.9, R103.1, U9.2, U37.4
pwm_ha: J4.5, R1.2, R5.1
pwm_ha_mcu: R1.1, U4.4, U45.2
pwm_hb: J4.7, R3.2, R7.1
pwm_hb_mcu: R3.1, U4.8
pwm_la: J4.6, R2.2, R6.1
pwm_la_mcu: R2.1, U4.5, U46.2
pwm_lb: J4.8, R4.2, R8.1
pwm_lb_mcu: R4.1, U4.9
rail_sense: C19.1, R27.2, U3.1
ref2v5: R82.2, R83.1, U13.1, U15.3
refin_n: R39.2, U30.6, U30.7
reset_clock: U20.1, U24.6
rim_buf_out: R98.1, U36.1, U36.4
rim_filt: C74.1, R97.2, U36.3, U40.4
rms_cavg: C82.1, U14.20
rms_core_in: C81.2, U14.3
rms_fb: R104.2, R105.1, U14.14
rms_ibuf: C81.1, U14.4, U14.5
rms_ignd: C83.1, R101.2, U14.12
rms_in: C80.2, R101.1, U14.6
rms_obuf: R104.1, R106.1, U14.15
rtd2_bias: R130.1, R137.2, R138.2, U50.4, U50.5
rtd2_force_n: C115.1, D13.3, J9.4, U50.12
rtd2_force_p: C112.1, D10.3, J9.1, U50.8
rtd2_refin_n: R130.2, U50.6, U50.7
rtd2_sense_n: C117.2, C119.1, R142.2, U50.11
rtd2_sense_n_ext: C114.1, D12.3, J9.3, R138.1, R140.1
rtd2_sense_n_mid: C116.2, R140.2, R142.1
rtd2_sense_p: C117.1, C118.1, R141.2, U50.10
rtd2_sense_p_ext: C113.1, D11.3, J9.2, R137.1, R139.1
rtd2_sense_p_mid: C116.1, R139.2, R141.1
rtd_food.adc-cs_n: R135.2, U50.16
rtd_food.adc-nc3: U50.20
rtd_food.adc-sclk: R132.2, U50.15
rtd_food.adc-sdi: R133.2, U50.14
rtd_food.adc-sdo: R134.1, U50.17
rtd_force_n: C45.1, D5.1, J3.4, U30.12
rtd_force_p: C42.1, D2.1, J3.1, U30.8
rtd_healthy: U22.5, U23.10
rtd_pan.adc-cs_n: R44.2, U30.16
rtd_pan.adc-nc3: U30.20
rtd_pan.adc-sclk: R42.2, U30.15
rtd_pan.adc-sdi: R43.2, U30.14
rtd_pan.adc-sdo: R45.1, U30.17
rtd_pan.high_window-out: U32.1, U33.2
rtd_pan.low_window-inp: C41.1, R51.2, U10.3, U31.3, U32.4
rtd_pan.low_window-out: U31.1, U33.1
rtd_pan.r_high_top-inp: R49.2, R50.1, U32.3
rtd_pan.rail_monitor-ct: U34.5
rtd_sense_n: C31.2, C40.1, R60.2, U30.11
rtd_sense_n_ext: C44.1, D4.1, J3.3, R41.1, R48.2, R58.1, R77.2
rtd_sense_n_mid: C38.2, R58.2, R60.1
rtd_sense_p: C31.1, C39.1, R59.2, U30.10
rtd_sense_p_ext: C43.1, D3.1, J3.2, R40.1, R51.1, R57.1
rtd_sense_p_mid: C38.1, R57.2, R59.1
runaway_healthy: U22.6, U23.12
rx_a_n: R78.2, R80.2, U5.2
rx_a_out: R80.1, R85.1, U5.1
rx_a_p: R79.2, R81.2, U5.3
rx_bias: R81.1, U5.6, U5.7
rx_bias_div: R83.2, R84.1, U5.5
selv_gnd: C1.2, C2.2, C4.2, C5.2, C6.2, C7.2, C8.2, C9.2, C10.2, C11.2, C13.2, C14.2, C15.2, C16.2, C17.2, C18.2, C19.2, C20.2, C21.2, C22.2, C23.2, C24.2, C25.2, C26.2, C27.2, C28.2, C29.2, C30.2, C32.2, C33.2, C34.2, C35.2, C36.2, C37.2, C39.2, C40.2, C41.2, C42.2, C43.2, C44.2, C45.2, C46.2, C47.2, C48.2, C49.2, C50.2, C51.2, C52.2, C53.2, C54.2, C55.2, C56.2, C57.2, C58.2, C59.2, C60.2, C61.2, C62.2, C63.2, C64.2, C65.2, C66.2, C67.2, C68.2, C69.2, C70.2, C71.2, C72.2, C73.2, C74.2, C75.2, C76.2, C77.2, C78.2, C79.2, C83.2, C84.2, C85.2, C86.2, C87.2, C88.2, C89.2, C90.2, C91.2, C92.2, C93.2, C94.2, C95.2, C96.2, C97.2, C110.2, C111.2, C112.2, C113.2, C114.2, C115.2, C118.2, C119.2, C120.2, C122.2, C123.2, C124.2, C125.2, C126.2, C127.2, C143.2, D1.2, D2.2, D3.2, D4.2, D5.2, D6.2, D7.2, D8.1, D10.1, D11.1, D12.1, D13.1, D14.2, D15.2, J1.2, J2.2, J4.2, J4.4, J4.15, J7.3, J7.5, J7.8, J7.11, J10.2, J11.5, J11.8, J12.2, J12.3, J13.2, J14.2, J15.1, J15.5, Q1.2, R5.2, R6.2, R7.2, R8.2, R12.2, R14.2, R16.2, R18.2, R19.2, R20.2, R24.2, R31.2, R35.2, R38.2, R50.2, R52.2, R54.2, R69.2, R70.2, R71.2, R72.2, R84.2, R86.2, R90.2, R100.2, R102.2, R103.2, R105.2, R110.2, R123.2, R151.2, R153.2, R154.2, U1.4, U2.4, U3.5, U4.1, U4.40, U4.41, U5.4, U6.4, U7.4, U8.2, U8.3, U8.12, U8.21, U9.1, U9.10, U9.19, U10.2, U11.3, U12.3, U13.2, U13.3, U14.9, U14.11, U15.4, U16.3, U17.2, U18.2, U19.2, U20.4, U21.2, U22.7, U23.7, U24.7, U24.13, U25.3, U26.2, U27.3, U28.3, U29.2, U30.9, U30.13, U30.18, U30.19, U31.2, U32.2, U33.3, U34.2, U35.3, U36.2, U37.3, U38.2, U39.2, U40.2, U41.3, U42.7, U43.3, U44.3, U45.3, U46.3, U50.9, U50.13, U50.18, U50.19, U51.4, U52.4
sense: R53.2, R54.1, U34.1
ss: C120.1, U51.7
ss_3v3: C2.1, U1.7
ss_12: C11.1, U2.7
sum: U14.1
sw_3v3: C3.2, L1.1, U1.5
sw_12: C12.2, L2.1, U2.5
sw_fan2: C121.2, L3.1, U51.5
u_3v3-rt: U1.1
u_12-rt: U2.1
u_cm_inv_ha-nc1: U45.1
u_cm_inv_la-nc1: U46.1
u_rail-ct: U3.3
u_rail_inv-nc1: U12.1
v3v3: C6.1, C7.1, C8.1, C20.1, C22.1, C24.1, C25.1, C26.1, C27.1, C28.1, C30.1, C32.1, C36.1, C37.1, C46.1, C47.1, C48.1, C49.1, C50.1, C51.1, C52.1, C53.1, C54.1, C55.1, C56.1, C57.1, C58.1, C60.1, C61.1, C63.1, C66.1, C69.1, C70.1, C75.1, C77.1, C79.1, C88.1, C89.1, C90.1, C92.1, C93.1, C94.1, C111.1, C126.1, D8.2, J4.3, J7.2, J11.1, L1.2, Q2.1, R13.1, R25.1, R27.1, R28.1, R29.1, R30.1, R33.1, R34.1, R37.1, R46.1, R55.1, R56.1, R61.1, R62.1, R63.1, R64.1, R65.1, R66.1, R67.1, R68.1, R73.1, R82.1, R93.1, R96.1, R99.1, R108.1, R109.1, R111.1, R112.1, R119.1, R120.1, R131.1, R136.1, R155.1, R156.1, R157.1, U3.2, U4.2, U5.8, U6.8, U7.8, U8.24, U9.20, U10.5, U11.5, U12.5, U15.8, U17.5, U18.5, U19.5, U20.2, U20.7, U20.8, U21.3, U21.5, U22.14, U23.14, U24.14, U25.5, U26.5, U27.5, U28.5, U29.3, U29.4, U30.2, U34.3, U34.4, U35.5, U36.5, U37.5, U38.5, U39.5, U40.5, U41.5, U42.1, U42.10, U42.14, U43.5, U44.5, U45.5, U46.5, U50.2, U52.3
v5_drop: C95.1, R122.2, U16.2
v5_mid: R121.2, R122.1
v15_selv: C1.1, C4.1, C5.1, C82.2, C85.1, C86.1, D9.1, R11.1, R121.1, U1.3, U14.16, U14.17, U14.18
vbias: R47.1, R49.1, U29.1
vbus_n: J4.12, R78.1
vbus_p: J4.11, R79.1
vref: U29.5
wdt_good: U9.6, U21.1, U25.1
y: R52.1, U33.4, U35.1
y6: U24.12

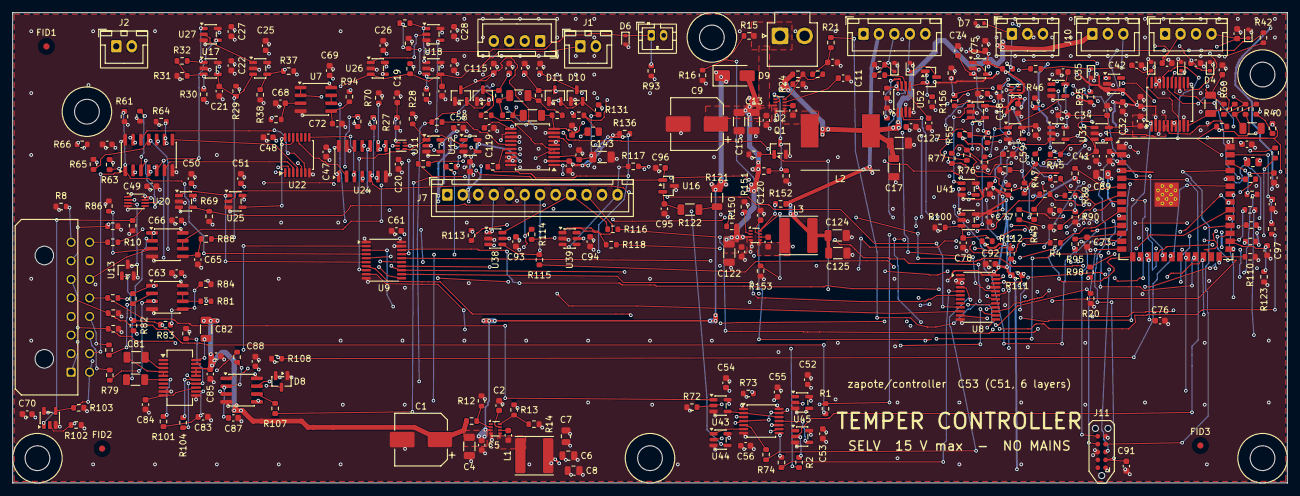
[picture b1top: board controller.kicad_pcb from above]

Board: 6 copper layers, 206.0 x 76.0 mm, 346 parts (0 on the bottom side), 212 nets.

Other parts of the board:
FID1, FID2, FID3: Fiducial_1mm_Mask2mm

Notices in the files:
README.md:
License: proprietary
